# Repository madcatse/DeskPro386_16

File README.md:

# DeskPro386_16
Compaq DeskPro 386/16 KiCad Schematic and PLD files

The Compaq DeskPro 386 was one of the first 80386/i386 PC Compatable computers.
It used mainly standard components found in the PC and PC-XT and used 14 
basic 20 and 24 pin Programmable Logic Devices (PLDS).
Later DeskPro 386 versions used VLSI 160+ pin chips unsuitable for use with breadboards.

Internal Compaq Design documents have been made available on Archive.org which
not only include more recent schematics than the original DeskPro 386/16 Technical Guide,
but also include the PLD Logic Rules and test vectors for all the chips in the PALASM language.

PALASM can be converted into CUPL for use with WinCUPL/II and modern ATF16V8B and ATF22V10C PLDs.

Compaq DeskPro 386/16 Technical Guide https://archive.org/details/compaq-desk-pro-386-technical-reference-guide-vol-1-1986-09
COmpaq DeskPro 386/16 Internal Design Document https://archive.org/details/compaq-desk-pro-386-technical-reference-guide-vol-1-1986-09

## KiCad Schematics
The Internal Design Document schematics have been reproduced in KiCad 10.
I have layed them out in one big diagram so that related pages are closer together to make tracing labels easier.
I find decomposed diagrams over many pages more difficult to understand.
Feel free to make a copy and re-organise if you feel differently.

Many of the chip symbols have been created to match the DeskPro schematics (DP in name) in the Breadboarding Symbol library (Breadboarding.kicad_sym).
You will need to configure the path to this library after opening the Project.

Use Preferences | Manage Symbol Libraries... then select the "Project Specific Libraries" tab
Select the path to the Breadboarding.kicad_sym file downloaded from GitHub.

Note many of the DP symbols have the power pins removed as this is what the DeskPro schematics did.
If you try to use these symbols for making a PCB be aware of the missing power pins and decoupling capacitors.

Symbols with BB in the name tend to match the physical pin layout so that the schematic can also be used for laying out breadboard designs.
The layout dimensions are very large (almost twice as big as A0 paper size) at 40" x 70".
PDF readers may have problems dealing with the schematic.

## Programmable Logic Definitions
There are two versions of the Internal Design Document, text mode and photo mode.
Generally I have used text mode to convert the content but sometimes photo mode is better.
The main issues in converting the logic definitions have been confusions between numeric 0 and letter O and letter l and numeric 1.
The test vectors have required quite a lot of massaging as PDF does not make it easy to copy the content due to it sometimes arranging text blocks in columns.
The PALASM folder has the text copies of the original PDF document in their original format (and with original typos and spelling mistakes).
The file extension .ASM is used as this is the recognised file extension for the CUPL 2.0 PTOC.EXE converter which converts PLDASM files into a .PLD logic definition and .SI simulation file.

THe ZIP file Logical_Devices_CUPL_v3.2b.zip contains an old version of CUPL (July 1990) which predates ATMEL/MicroChip and include the PTOC.EXE utility used to convert PALASM in CUPL format files.

More folders will be added with the .PLD logic definition and .SI simulation files as these are migrated and tested.

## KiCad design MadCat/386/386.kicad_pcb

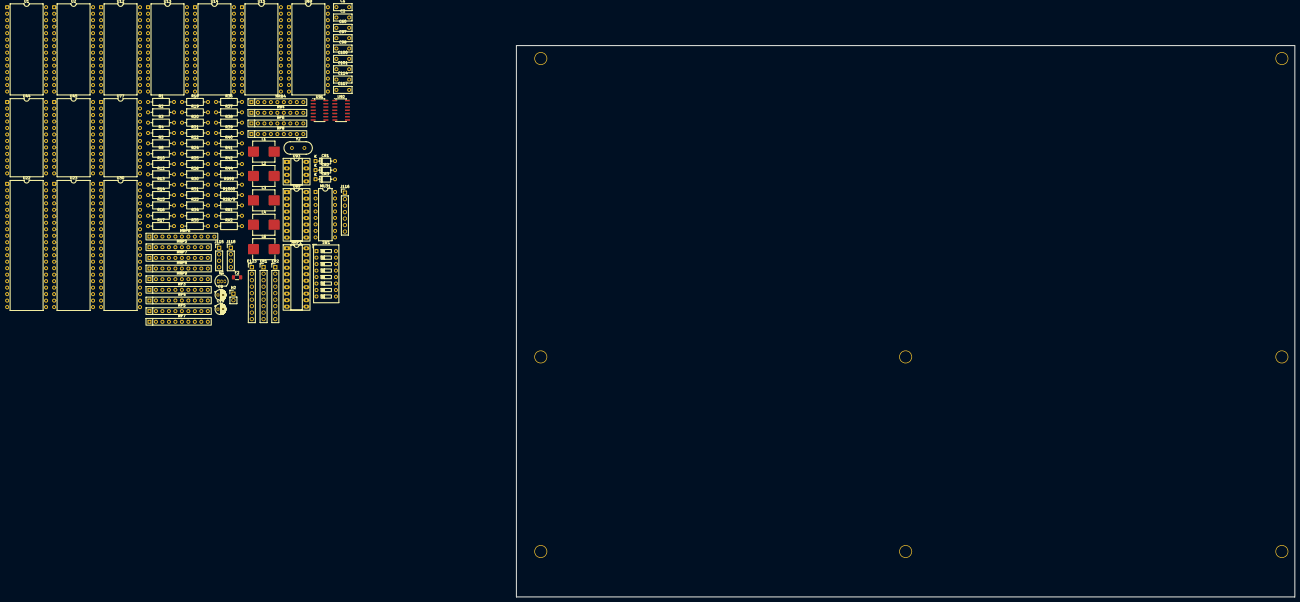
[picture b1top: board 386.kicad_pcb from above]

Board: 2 copper layers, 304.8 x 215.9 mm, 109 parts (0 on the bottom side), 143 nets, no tracks yet.

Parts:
C1, C2, C60, C114: 47pF; C_Disc_D7.0mm_W2.5mm_P5.00mm
C9, C19: 10uF; CP_Radial_D4.0mm_P2.00mm
C97: 0.001uF; C_Disc_D7.0mm_W2.5mm_P5.00mm
C98, C101: 0.047uF; C_Disc_D7.0mm_W2.5mm_P5.00mm
C100: 10pF; C_Disc_D7.0mm_W2.5mm_P5.00mm
C117: 18pF; C_Disc_D7.0mm_W2.5mm_P5.00mm
CR1, CR2, CR3: 1N914; D_DO-35_SOD27_P7.62mm_Horizontal
E123: Conn_01x09_Pin; PinHeader_1x09_P2.54mm_Vertical
ER1, ER2: Conn_01x09_Pin; PinHeader_1x09_P2.54mm_Vertical
F2: F 5A; Fuse_1206_3216Metric
H1, H2#2, H3, H5, H6, H7, H8, H9: HOLE1; HOLE
H2: KEYLOCK; PinHeader_1x02_P2.54mm_Vertical
J115: SPEAKER; PinHeader_1x04_P2.54mm_Vertical
J116: KEYBOARD; PinHeader_1x07_P2.54mm_Vertical
J118: BATTERY; PinHeader_1x04_P2.54mm_Vertical
L1, L2, L3, L4, L6: FerriteBead; L_Panasonic_PCC-M0850M
MRB4: 33R; R_Array_SIP9
MRP1: 33R; DIP-20_W7.62mm_Socket_LongPads
MRP5, MRP7, MRP8, MRP9: 4K7; R_Array_SIP10
MRP6: 8K2; R_Array_SIP11
MU31: 51256-10; DIP-16_W7.62mm
Q1: TL431LP; TO-92_Inline
R1: 87K; R_Axial_DIN0207_L6.3mm_D2.5mm_P10.16mm_Horizontal
R2: 48K; R_Axial_DIN0207_L6.3mm_D2.5mm_P10.16mm_Horizontal
R3: 270R; R_Axial_DIN0207_L6.3mm_D2.5mm_P10.16mm_Horizontal
R4: 4K7; R_Axial_DIN0207_L6.3mm_D2.5mm_P10.16mm_Horizontal
R5, R12, R16, R20, R21, R24: 1K; R_Axial_DIN0207_L6.3mm_D2.5mm_P10.16mm_Horizontal
R8, R25, R26: 30R; R_Axial_DIN0207_L6.3mm_D2.5mm_P10.16mm_Horizontal
R10, R13, R18, R28/9, R30, R42: 180R; R_Axial_DIN0207_L6.3mm_D2.5mm_P10.16mm_Horizontal
R14, R41, R999, R1000: 20K; R_Axial_DIN0207_L6.3mm_D2.5mm_P10.16mm_Horizontal
R15, R22: 8K2; R_Axial_DIN0207_L6.3mm_D2.5mm_P10.16mm_Horizontal
R17: 22M; R_Axial_DIN0207_L6.3mm_D2.5mm_P10.16mm_Horizontal
R19: 470K; R_Axial_DIN0207_L6.3mm_D2.5mm_P10.16mm_Horizontal
R31, R33, R36, R38: 68R; R_Axial_DIN0207_L6.3mm_D2.5mm_P10.16mm_Horizontal
R34, R35: 22R; R_Axial_DIN0207_L6.3mm_D2.5mm_P10.16mm_Horizontal
R37: 51R; R_Axial_DIN0207_L6.3mm_D2.5mm_P10.16mm_Horizontal
R39, R40: 10K; R_Axial_DIN0207_L6.3mm_D2.5mm_P10.16mm_Horizontal
R44: 60R; R_Axial_DIN0207_L6.3mm_D2.5mm_P10.16mm_Horizontal
RB4: 33R; R_Array_SIP9
RP3, RP4, RP5: 8K2; R_Array_SIP10
RP6, RP8: 8K2; R_Array_SIP9
RP7: 20K; R_Array_SIP10
RX1, RX2: 20K; R_Axial_DIN0207_L6.3mm_D2.5mm_P10.16mm_Horizontal
SW1: SW_DIP_x08; SW_DIP_SPSTx08_Slide_9.78x22.5mm_W7.62mm_P2.54mm
U1, U2: 8259A-2; DIP-28_W15.24mm
U12, U13, U14, U15: 2764; DIP-28_W15.24mm
U22, U23: 8237A; DIP-40_W15.24mm
U30: 74LS612; DIP-40_W15.24mm
U44, U45: 8254; DIP-24_W15.24mm
U69: 74F74; DIP-28_W15.24mm
U77: MC146818; DIP-24_W15.24mm
U89: 74F175BB; DIP-16_W7.62mm_Socket_LongPads
U91: 74ALS1035; SOIC-14_3.9x8.7mm_P1.27mm
U92: 74F11; SOIC-14_3.9x8.7mm_P1.27mm
U93: SN75477; DIP-8_W7.62mm_Socket_LongPads
Y2: 32.76KHz; Crystal_HC49-U_Vertical

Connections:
+5V: CR2.2 (A), E123.1, E123.4, E123.7, F2.2, J115.1, MRP5.1 (common), MRP6.1 (R1), MRP7.1 (common), MRP8.1 (common), MRP9.1 (common), R4.1, R5.2, R16.1, R22.2, R24.1, R40.1, R41.1, R999.2, R1000.2, RP3.1 (common), RP4.1 (common), RP6.1 (R1), RP7.1 (common), RP8.1 (R1), RX1.2, RX2.2, U1.16 (~SP/~EN), U1.28 (VCC), U2.28 (VCC), U12.1 (VPP), U13.1 (VPP), U14.1 (VPP), U15.1 (VPP), U30.28 (C), U30.40 (VCC), U44.11 (G0), U44.14 (G1), U44.24 (VCC), U45.11 (G0), U45.14 (G1), U45.24 (VCC), U69.1 (~R), U69.4 (~S), U91.14 (VCC), U93.5 (CLAMP), U93.8 (VCC)
/+KB: J116.2, L6.1
/-KB: J116.5, J116.6, L3.2
/CAS0: U1.12 (CAS0), U2.12 (CAS0)
/CAS1: U1.13 (CAS1), U2.13 (CAS1)
/CAS2: U1.15 (CAS2), U2.15 (CAS2)
/DAE2: U23.9 (AEN), U92.4
/DRQ0: RP5.7 (R6), U22.19 (DREQ0)
/DRQ1: RP5.8 (R7), U22.18 (DREQ1)
/DRQ2: RP5.10 (R9), U22.17 (DREQ2)
/DRQ3: RP5.9 (R8), U22.16 (DREQ3)
/DRQ4: U22.10 (HRQ), U23.19 (DREQ0)
/DRQ5: RP5.6 (R5), U23.18 (DREQ1)
/DRQ6: RP5.5 (R4), U23.17 (DREQ2)
/DRQ7: RP5.4 (R3), U23.16 (DREQ3)
/FAILTM: SW1.1, U44.10 (OUT0)
/IOD0: U1.11 (D0), U2.11 (D0), U22.30 (DB0), U23.30 (DB0), U30.7 (D0), U44.8 (D0), U45.8 (D0), U77.4 (AD0)
/IOD1: U1.10 (D1), U2.10 (D1), U22.29 (DB1), U23.29 (DB1), U30.8 (D1), U44.7 (D1), U45.7 (D1), U77.5 (AD1)
/IOD2: U1.9 (D2), U2.9 (D2), U22.28 (DB2), U23.28 (DB2), U30.9 (D2), U44.6 (D2), U45.6 (D2), U77.6 (AD2)
/IOD3: U1.8 (D3), U2.8 (D3), U22.27 (DB3), U23.27 (DB3), U30.10 (D3), U44.5 (D3), U45.5 (D3), U77.7 (AD3)
/IOD4: U1.7 (D4), U2.7 (D4), U22.26 (DB4), U23.26 (DB4), U30.11 (D4), U44.4 (D4), U45.4 (D4), U77.8 (AD4)
/IOD5: U1.6 (D5), U2.6 (D5), U22.23 (DB5), U23.23 (DB5), U30.12 (D5), U44.3 (D5), U45.3 (D5), U77.9 (AD5)
/IOD6: U1.5 (D6), U2.5 (D6), U22.22 (DB6), U23.22 (DB6), U30.29 (D6), U44.2 (D6), U45.2 (D6), U77.10 (AD6)
/IOD7: U1.4 (D7), U2.4 (D7), U22.21 (DB7), U23.21 (DB7), U30.30 (D7), U44.1 (D7), U45.1 (D7), U77.11 (AD7)
/IRQ0: U1.18 (IR0), U45.10 (OUT0)
/IRQ2: U1.20 (IR2), U2.17 (INT)
/KEY: J115.3, J116.3
/KEYCLK: C1.2, L2.1, RP8.2 (R1.2), U91.8
/KEYDAT: C114.2, L4.1, RP8.3 (R2.2), U91.6
/KRS: J116.1, RP8.4 (R3.2)
/MA0: MRP1.2 (R2.1), MU31.5 (A_{0})
/MA1: MRP1.3 (R3.1), MU31.7 (A_{1})
/MA2: MRP1.4 (R4.1), MU31.6 (A_{2})
/MA3: MRP1.5 (R5.1), MU31.12 (A_{3})
/MA4: MRP1.6 (R6.1), MU31.11 (A_{4})
/MA5: MRP1.7 (R7.1), MU31.10 (A_{5})
/MA6: MRP1.8 (R8.1), MU31.13 (A_{6})
/MA7: MRP1.9 (R9.1), MU31.9 (A_{7})
/MA8: MRP1.10 (R10.1), MU31.1 (A_{8})
/MD0: MRP5.10 (R9), MRP7.10 (R9), MRP8.10 (R9), MU31.2 (Din), MU31.14 (Dout)
/MD1: MRP5.9 (R8), MRP7.9 (R8), MRP8.9 (R8)
/MD2: MRP5.8 (R7), MRP7.8 (R7), MRP8.8 (R7)
/MD3: MRP5.7 (R6), MRP7.7 (R6), MRP8.7 (R6)
/MD4: MRP5.6 (R5), MRP7.6 (R5), MRP8.6 (R5)
/MD5: MRP5.5 (R4), MRP7.5 (R4), MRP8.5 (R4)
/MD6: MRP5.4 (R3), MRP7.4 (R3), MRP8.4 (R3)
/MD7: MRP5.3 (R2), MRP7.3 (R2), MRP8.3 (R2)
/N9: J116.7, L2.2
/N10: J116.4, L4.2
/RD0: U12.11 (D0), U13.11 (D0)
/RD1: U12.12 (D1), U13.12 (D1)
/RD2: U12.13 (D2), U13.13 (D2)
/RD3: U12.15 (D3), U13.15 (D3)
/RD4: U12.16 (D4), U13.16 (D4)
/RD5: U12.17 (D5), U13.17 (D5)
/RD6: U12.18 (D6), U13.18 (D6)
/RD7: U12.19 (D7), U13.19 (D7)
/RD8: U14.11 (D0), U15.11 (D0)
/RD9: U14.12 (D1), U15.12 (D1)
/RD10: U14.13 (D2), U15.13 (D2)
/RD11: U14.15 (D3), U15.15 (D3)
/RD12: U14.16 (D4), U15.16 (D4)
/RD13: U14.17 (D5), U15.17 (D5)
/RD14: U14.18 (D6), U15.18 (D6)
/RD15: U14.19 (D7), U15.19 (D7)
/REND: U89.11 (~Q), U89.13 (D)
/RM1A13: ER1.2, U13.26 (A13/CS1), U15.26 (A13/CS1)
/RM1A14: ER1.5, U13.27 (A14/CS2), U15.27 (A14/CS2)
/RM2A13: ER2.2, U12.26 (A13/CS1), U14.26 (A13/CS1)
/RM2A14: ER2.5, U12.27 (A14/CS2), U14.27 (A14/CS2)
/RRQ: U89.2 (Q), U89.5 (D)
/SA1: U12.10 (A0), U13.10 (A0), U14.10 (A0), U15.10 (A0)
/SA2: U12.9 (A1), U13.9 (A1), U14.9 (A1), U15.9 (A1)
/SA3: U12.8 (A2), U13.8 (A2), U14.8 (A2), U15.8 (A2)
/SA4: U12.7 (A3), U13.7 (A3), U14.7 (A3), U15.7 (A3)
/SA5: U12.6 (A4), U13.6 (A4), U14.6 (A4), U15.6 (A4)
/SA6: U12.5 (A5), U13.5 (A5), U14.5 (A5), U15.5 (A5)
/SA7: U12.4 (A6), U13.4 (A6), U14.4 (A6), U15.4 (A6)
/SA8: U12.3 (A7), U13.3 (A7), U14.3 (A7), U15.3 (A7)
/SA9: U12.25 (A8), U13.25 (A8), U14.25 (A8), U15.25 (A8)
/SA10: U12.24 (A9), U13.24 (A9), U14.24 (A9), U15.24 (A9)
/SA11: U12.21 (A10), U13.21 (A10), U14.21 (A10), U15.21 (A10)
/SA12: U12.23 (A11), U13.23 (A11), U14.23 (A11), U15.23 (A11)
/SA13: U12.2 (A12), U13.2 (A12), U14.2 (A12), U15.2 (A12)
/SA14: ER1.3, ER2.3
/SA15: ER1.6, ER2.6
/SPKRCK: U45.17 (OUT2), U93.1 (S)
/SPKRDT: U93.2 (1A), U93.7 (2A)
/V2P5R: C9.2, Q1.1 (REF), R1.1, R2.2
/V5CMOS: C19.1, C101.2, CR1.1 (K), CR2.1 (K), CR3.1 (K), R20.2, U77.20 (CKFS), U77.24 (VCC)
/XA0: U1.27 (A0), U2.27 (A0), U22.32 (A0), U30.36 (RS0), U44.19 (A0), U45.19 (A0)
/XA1: U22.33 (A1), U23.32 (A0), U30.38 (RS1), U44.20 (A1), U45.20 (A1)
/XA2: U22.34 (A2), U23.33 (A1), U30.1 (RS2)
/XA3: U22.35 (A3), U23.34 (A2), U30.3 (RS3)
/XA4: U22.37 (A4), U23.35 (A3)
/XA5: U22.38 (A5), U23.37 (A4)
/XA6: U22.39 (A6), U23.38 (A5)
/XA7: U22.40 (A7), U23.39 (A6)
/ZCK32: R38.1, U69.3 (C)
/ZCLK16: R35.1, U69.6 (~Q)
/~CMSCE: U77.13 (~CE), U77.16 (STBY)
/~DAK4: U23.25 (DACK0), U30.2 (MA3), U92.5
/~EP1: RP6.7 (R6.2), U22.36 (~EOP)
/~EP2: RP6.8 (R7.2), U23.36 (~EOP)
/~RM1CS: ER1.8, U13.20 (~CE), U15.20 (~CE)
/~RM1OE: ER1.9, U13.22 (~OE), U15.22 (~OE)
/~RM2CS: ER2.8, U12.20 (~CE), U14.20 (~CE)
/~RM2OE: ER2.9, U12.22 (~OE), U14.22 (~OE)
/~ROM: ER1.7, ER2.7
/~TRDY: R33.1, U92.12
<NO NET>: H2.2 (B), SW1.10, SW1.11, SW1.12, SW1.13, SW1.14, SW1.15
BCLK: C60.1, L1.2, U89.9 (CLK)
CKM: RP8.6 (R5.2), SW1.3
CLK16: R35.2, U69.2 (D)
DCLK: R25.2, U22.12 (CLK), U23.12 (CLK), U44.18 (CLK2)
DRDY: U22.6 (READY), U23.6 (READY)
GND: C1.1, C2.1, C19.2, C60.2, C98.1, C100.1, C101.1, C114.1, C117.1, E123.3, E123.6, E123.9, ER1.1, ER1.4, ER2.1, ER2.4, H1.1, H2#2.1, H3.1, H5.1, H6.1, H7.1, H8.1, H9.1, J115.2, J118.4, L3.1, Q1.2 (A), R1.2, R10.1, R12.1, R13.1, R14.2, R15.1, R18.1, R21.2, R28/9.2, R30.2, R39.1, R42.1, RP5.1 (common), U1.14 (GND), U2.14 (GND), U2.16 (~SP/~EN), U30.13 (~MM), U30.20 (GND), U30.31 (D8), U30.32 (D9), U30.33 (D10), U30.34 (D11), U44.12 (GND), U45.12 (GND), U77.1 (MOT), U77.12 (GND), U91.7 (GND), U93.4 (GND)
unnamed: C97.2, R39.2, R40.2
unnamed: C100.2, R17.1, Y2.1
unnamed: C117.2, R19.1, Y2.2
unnamed: CR1.2 (A), J118.1
unnamed: C9.1, CR3.2 (A), Q1.3 (K), R2.1, R3.1
unnamed: F2.1, L6.2
unnamed: J115.4, R44.1
unnamed: R17.2, R19.2
unnamed: C98.2, R20.1, U77.18 (~RESET), U77.22 (PS)
unnamed: C2.2, R44.2, U93.3 (1Y), U93.6 (2Y)
RESDRV: U22.13 (RESET), U23.13 (RESET)
TIMCLK: U44.9 (CLK0), U44.15 (CLK1), U45.9 (CLK0), U45.15 (CLK1), U45.18 (CLK2)
TST1: MRP6.9 (R8.2), R18.2
TST2: MRP6.10 (R9.2), R10.2
~CRDY: R41.2, U92.13
~DMRDC: RP6.2 (R1.2), U22.3 (~MEMR), U23.3 (~MEMR)
~HITIM: RP8.8 (R7.2), SW1.16
~INTA: U1.26 (~INTA), U2.26 (~INTA)
~MRDY: RP7.7 (R6), U92.1
~NCPIN: RP8.7 (R6.2), SW1.2
~RST: R24.2, U89.1 (~CLR)
~WE0: MRP1.1 (R1.1), MU31.3 (~WE)
~XIORC: RP6.4 (R3.2), U1.3 (~RD), U2.3 (~RD), U22.1 (~IOR), U23.1 (~IOR), U44.22 (~RD), U45.22 (~RD)
~XIOWC: RP6.3 (R2.2), U1.2 (~WR), U2.2 (~WR), U22.2 (~IOW), U23.2 (~IOW), U30.5 (~STROBE), U44.23 (~WR), U45.23 (~WR)
~XMWTC: RP6.5 (R4.2), U22.4 (~MEMW), U23.4 (~MEMW)
~ZCK16: R34.1, U69.5 (Q)

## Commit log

2026-05-01 Initial upload of KiCad Schematic and PALASM files
    KiCad 10 format schematic and PALASM Logic definitions and test vectors for DeskPro 386/16
2026-05-01 Update README.md
    Update for heading formatting
2026-05-05 Small update
2026-05-06 Cloning
